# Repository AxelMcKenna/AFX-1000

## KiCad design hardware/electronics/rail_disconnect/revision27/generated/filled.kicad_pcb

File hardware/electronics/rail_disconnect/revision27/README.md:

# E27 disconnect qualification audit and routing candidate

E27 is a separate development candidate, preserving E26, E25 and A11. It retains the 164-part pin/value circuit, all component/pad positions, outline, mounts and bulk-capacitor poses. It adds 925 trace segments and 22 conventional vias over E26: **8,860 segments and 518 vias**. Native checking reports **8 open connections, 21 DRC warnings and zero parity issues**, compared with E26's 21 opens and 30 warnings. The remaining warnings are 20 dangling tracks and one copper sliver. The strict checker fails; this is not a fabrication or full qualification pass.

The repaired main header paths include N12_SRC and N19. Missing OV, reference, allow and MCAP branches remain critical: they can prevent or defeat the power interlock. Do not interpret the smaller open count as a safe power-up release. Every physical, copper-loss, thermal, startup, fabrication and build-ready flag remains false.

## What was actually checked and changed

`native_graph.py` exports connected-component anchors from KiCad's actual connectivity engine and freshly filled board. The bounded repair uses those anchors, rather than assuming the reported nearest airwire endpoints are usable escape points. All additions are ordinary traces/vias; no jumper component or ignored DRC rule closes a net. `reviewed-additions.json` and `replay.py` reconstruct the editable PCB byte-for-byte from frozen E26 plus the exact added copper objects.

Some new traces use In1.Cu, cutting clearances into its AGND pour. In4.Cu remains the other ground plane. This changes return-plane usage and has **not** been qualified for reference impedance, noise or EMI. No component moves or new mechanical clearance claims are made. The proposed P02 strap/stud interfaces are still absent.

A trial that allowed signal routes to cut power pours introduced new power-net opens; that trial was rejected. Short experiment records remain under `generated/experiments/`. The selected board preserves the power-pour reservations, uses the additional inner-layer escapes and retains every actual native finding.

## Actual filled-copper diagnostic

`copper.py` builds a finite-volume resistor network from native **filled polygons**, actual traces and lands, and finite cylindrical plated barrels. It does not replace fills with ideal ribbon rectangles. Assumed process values are 70 µm finished copper, 25 µm plating and 85 °C copper. The PCB has **no specified dielectric stackup**; equal layer spacing is an explicit placeholder for the barrel calculation.

| Positive path, excluding MOSFET channels | 0.20 mm grid | 0.10 mm grid | P02 allocation |
| --- | ---: | ---: | ---: |
| Analog source + common + output | 3.169 mΩ | 3.140 mΩ | ≤3.000 mΩ |
| Digital source + common + output | 1.055 mΩ | 1.017 mΩ | ≤3.000 mΩ |

The analog diagnostic exceeds the allocation at both resolutions. This is a model concern requiring layout/process refinement and a bounded extraction, not an independently certified resistance failure. Rounded lands are rectangularized, cell-center discretization is approximate, annuli/contact regions are idealized, and parallel FET terminal groups are equipotential electrodes. The digital result therefore **does not bound unequal or diagonal switch current sharing**.

The header-return diagnostic uses 0.40/0.20 mm grids. Its finer values are approximately 0.632 mΩ J1→J3 analog return, 0.275 mΩ J2→J4 digital return, and 0.814 mΩ between the protected analog/digital ground headers. These are two-terminal pair resistances under the same approximations, **not multiport transfer impedances or the full P02 strap/contact paths**. No unimplemented stud region is treated as a real electrical terminal. Real four-wire, temperature and current-sharing measurements remain required.

## Manufacturer findings

The [Skyworks Si8751 datasheet](https://www.skyworksinc.com/-/media/SkyWorks/SL/documents/public/data-sheets/Si8751-2.pdf) gives the reviewed timing conditions at a 100 pF gate load. The existing TT=10 kΩ circuit is checked against its static gate-voltage/impedance entries; those values do not bound the actual switch waveform. The [TI CSD18510Q5B table](https://www.ti.com/lit/ds/symlink/csd18510q5b.pdf) gives up to 153 nC at its stated 10 V gate / 20 V drain / 32 A test point. Four digital FETs give a 612 nC comparison, 612 times the 100 pF-at-10 V test charge. That comparison is not an actual application gate-charge measurement or a scaled timing guarantee. The [CSD18540Q5B](https://www.ti.com/lit/ds/symlink/csd18540q5b.pdf) has its own stated test conditions and SOA.

All 14 FET footprints have generic **0.70 × 0.70 mm** source/gate lands. TI's CSD18510Q5B recommended pattern, section 7.2, specifies **1.100 × 0.710 mm** for those lands. The footprints are not that recommended pattern, and no alternate assembly/manufacturer approval is recorded. Pin roles match the reviewed top-view diagram, but terminal tolerances, complete compound drain shape, mask and stencil still need a coordinated land-pattern review and correction/approval. The larger TI compound drain drawing must not be compared as if it were merely the generic footprint's central exposed-pad rectangle.

The native C24 bulk is 4,700 µF ±20%. At the maximum local capacitance and 5.1 V, stored energy is 73.35 mJ; a hypothetical 1 ms linear ramp needs 28.764 A average before load or downstream capacitors. This is not a predicted waveform. The interlock has no independent current limiter, and upstream soft start does not constrain a later FET closure. Avalanche energy is not the linear SOA needed to approve that event. Measure actual VDS, ID and VGS simultaneously and assess the hot transient operating locus.

This board provides a level-controlled **overvoltage-only** interlock. It adds no undervoltage qualification or separate fault latch. Opening the switches does not establish rapid bulk discharge or isolation of every signal-pin backfeed path.

## Reproduce

```sh
uv run --locked python -m hardware.electronics.rail_disconnect.revision27.replay --check
uv run --locked python -m hardware.electronics.rail_disconnect.revision27.check --kicad-cli /path/to/kicad-cli
# Strict native check above intentionally fails while the reported findings remain.
uv run --locked python -m hardware.electronics.rail_disconnect.revision27.device_review
uv run --locked python -m hardware.electronics.rail_disconnect.revision27.copper --steps .2,.1
uv run --locked python -m hardware.electronics.rail_disconnect.revision27.copper --returns
uv run --locked python -m unittest discover -s tests/tooling -p test_disconnect_revision27.py -v
uv run --locked python -m hardware.electronics.rail_disconnect.revision27.qualify
```

`native_graph.py` requires KiCad's supplied Python/pcbnew; the copper diagnostic requires NumPy. Tests independently check exact series/parallel networks, finite barrel resistance, missing-via disconnection, gate/energy scaling, byte-exact replay, parent-item preservation and rejection of suppressed native findings. Synthetic solver fixtures are not physical captures.

`generated/qualification.json` binds the source, native findings and diagnostic outputs without converting them into measured results. Manufacturer/fabricator approval, complete routing, a specified stackup, actual copper/contact bounds, late-closure SOA, thresholds/timing, partial-power behavior, thermal/EMI and complete-system physical measurements are still required.

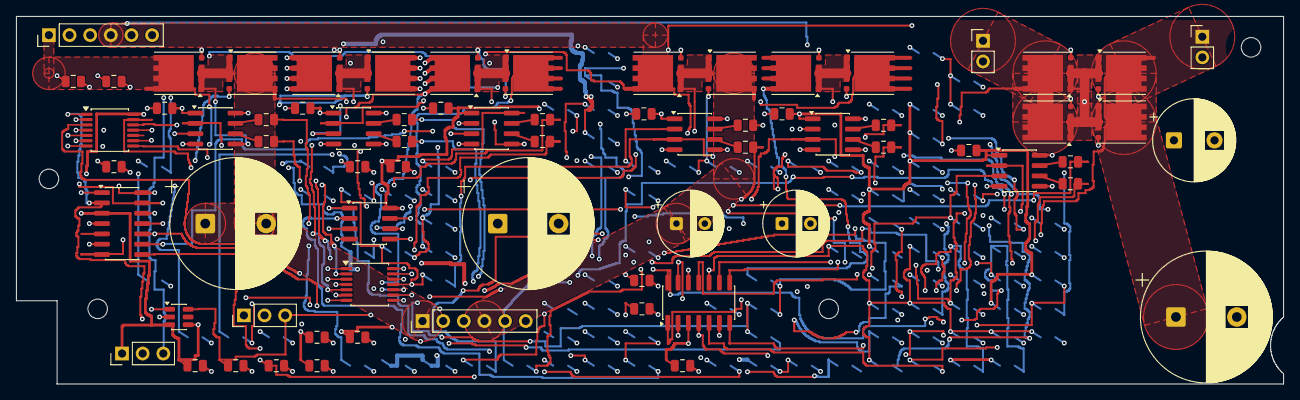
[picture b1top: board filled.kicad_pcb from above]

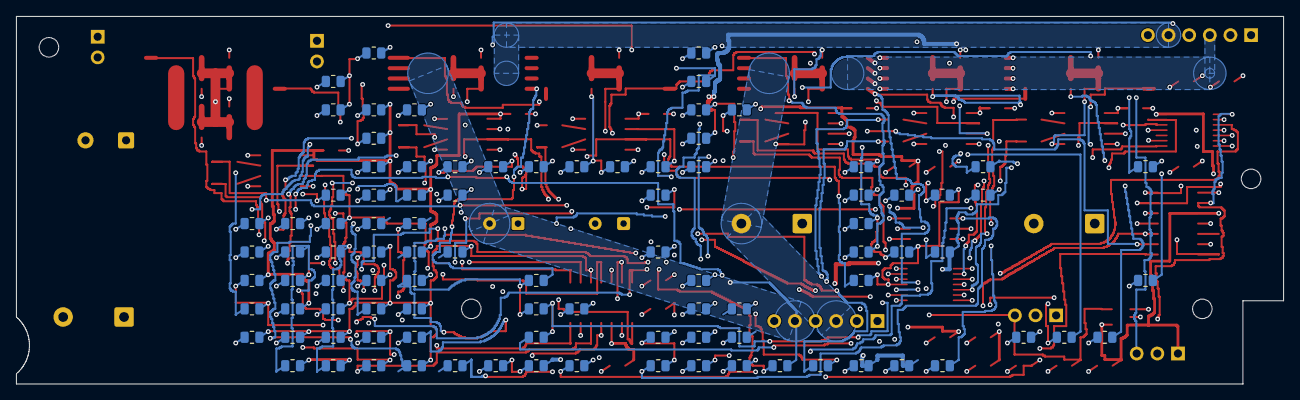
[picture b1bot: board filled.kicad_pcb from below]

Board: 6 copper layers, 156.0 x 45.2 mm, 168 parts (94 on the bottom side), 108 nets.

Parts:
C1, C5, C9, C13, C17, C21, C25, C29, C34, C35, C36, C37: 100nF 16V X7R; C_0805_2012Metric
C2, C3, C6, C7, C10, C11, C14, C15, C18, C19, C22, C23: 10pF 100V C0G 5%; C_0805_2012Metric
C4, C8: 1500uF 35V electrolytic 20% EEUFR1V152S; CP_Radial_D16.0mm_P7.50mm
C12, C16: 220uF 35V electrolytic 20% EEUFR1V221; CP_Radial_D8.0mm_P3.50mm
C20: 1500uF 16V electrolytic 20% EEUFR1C152; CP_Radial_D10.0mm_P5.00mm
C24: 4700uF 16V electrolytic 20% EEUFR1C472; CP_Radial_D16.0mm_P7.50mm
C26: 1uF 16V X7R; C_0805_2012Metric
C27, C28, C30, C31, C32, C33: 100pF 50V C0G 5%; C_0805_2012Metric
C38: 10uF 16V X7R; C_0805_2012Metric
H1, H2, H3, H4: M2_CLEARANCE; M2_Clearance
J1, J3: Header6; PinHeader_1x06_P2.54mm_Vertical
J2, J4: Header2; PinHeader_1x02_P2.54mm_Vertical
J5, J6: Header3; PinHeader_1x03_P2.54mm_Vertical
Q1, Q2, Q3, Q4, Q5, Q6, Q7, Q8: CSD18540Q5B; VSONP-8-1EP_5x6_P1.27mm
Q9, Q10, Q11, Q12, Q13, Q14: CSD18510Q5B; VSONP-8-1EP_5x6_P1.27mm
R1, R9, R17, R25, R33, R41: 22 1%; R_0805_2012Metric
R2, R10, R18, R26, R34, R42, R60, R63, R68, R71, R76, R81, R86, R91: 20M 1%; R_0805_2012Metric
R3, R5, R11, R13, R19, R21, R27, R29, R35, R37, R43, R45, R61, R64, R69, R72, R77, R82, R87, R92: 10k 1%; R_0805_2012Metric
R4, R12, R20, R28, R36, R44: 100 1%; R_0805_2012Metric
R6, R7, R14, R15, R22, R23, R30, R31, R38, R39, R46, R47: 15k 1%; R_0805_2012Metric
R8, R16, R24, R32, R40, R48: 47k 1%; R_0805_2012Metric
R49: 150k 0.01% 5ppm; R_0805_2012Metric
R50: 6.2k 0.01% 5ppm; R_0805_2012Metric
R51, R54, R58, R59, R62, R66, R67, R70, R74, R75, R79, R80, R84, R85, R89, R90, R94: 10k 0.01% 5ppm; R_0805_2012Metric
R52, R55: 1k 1%; R_0805_2012Metric
R53: 100k 0.01% 5ppm; R_0805_2012Metric
R56: 143k 0.01% 5ppm; R_0805_2012Metric
R57: 3.3k 0.01% 5ppm; R_0805_2012Metric
R65: 90.9k 0.01% 5ppm; R_0805_2012Metric
R73, R78: 31.6k 0.01% 5ppm; R_0805_2012Metric
R83: 12.4k 0.01% 5ppm; R_0805_2012Metric
R88: 7.5k 0.01% 5ppm; R_0805_2012Metric
R93: 100k 1%; R_0805_2012Metric
U1, U2, U3, U4, U5, U6: SI8751AB-ISR; SOIC-8_3.9x4.9mm_P1.27mm
U7: REF35125QDBVR; SOT-23-6
U8: OPA2333AID; SOIC-8_3.9x4.9mm_P1.27mm
U9, U10: TLV1824IDR; SOIC-14_3.9x8.7mm_P1.27mm
U11, U12: SN74LVC08APWR; TSSOP-14_4.4x5mm_P0.65mm

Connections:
/5V_DIG: C24.1, J4.1, Q12.3, Q14.3, R47.1, R48.1
/5V_DIG_ALLOW: R44.2, R45.1, U6.3
/5V_DIG_COMMON: Q11.1, Q12.1, Q13.1, Q14.1, R42.2, U6.5
/5V_DIG_DRIVE: R41.1, U6.8
/5V_DIG_GATE: Q11.2, Q12.2, Q13.2, Q14.2, R41.2, R42.1
/5V_DIG_MCAP1: C22.2, U6.7
/5V_DIG_MCAP1_LIMIT: C22.1, R46.2
/5V_DIG_MCAP2: C23.2, U6.6
/5V_DIG_MCAP2_LIMIT: C23.1, R47.2
/5V_DIG_OV_OK: R81.1, R82.2, U10.1, U11.10
/5V_DIG_OV_REF: R80.2, R81.2, U10.7
/5V_DIG_OV_SENSE: C33.1, R78.2, R79.1, U10.6
/5V_DIG_SRC: J2.1, Q11.3, Q13.3, R46.1, R78.1
/5V_DIG_TT: R43.1, U6.2
/AGND: C1.2, C4.2, C5.2, C8.1, C9.2, C12.2, C13.2, C16.1, C17.2, C20.2, C21.2, C24.2, C25.2, C26.2, C27.2, C28.2, C29.2, C30.2, C31.2, C32.2, C33.2, C34.2, C35.2, C36.2, C37.2, C38.2, J1.2, J2.2, J3.2, J4.2, J5.2, J6.1, R3.2, R5.2, R8.2, R11.2, R13.2, R16.2, R19.2, R21.2, R24.2, R27.2, R29.2, R32.2, R35.2, R37.2, R40.2, R43.2, R45.2, R48.2, R58.2, R66.2, R74.2, R79.2, R84.2, R89.2, R93.2, R94.2, U1.4, U2.4, U3.4, U4.4, U5.4, U6.4, U7.1, U7.2, U8.3, U8.4, U8.5, U9.12, U10.12, U11.7, U12.7
/ALL_RAILS_ALLOW: J6.2, R4.1, R12.1, R20.1, R28.1, R36.1, R44.1, U12.11
/N12: C16.2, J3.5, Q8.3, R31.1, R32.1
/N12_ALLOW: R28.2, R29.1, U4.3
/N12_COMMON: Q7.1, Q8.1, R26.2, U4.5
/N12_DRIVE: R25.1, U4.8
/N12_GATE: Q7.2, Q8.2, R25.2, R26.1
/N12_INV: R54.1, R55.1, U8.7
/N12_MCAP1: C14.2, U4.7
/N12_MCAP1_LIMIT: C14.1, R30.2
/N12_MCAP2: C15.2, U4.6
/N12_MCAP2_LIMIT: C15.1, R31.2
/N12_OV_OK: R71.1, R72.2, U9.13, U11.5
/N12_OV_REF: R70.2, R71.2, U9.11
/N12_OV_SENSE: C28.1, R55.2, U9.10
/N12_SRC: J1.5, Q7.3, R30.1, R53.1
/N12_SUM: R53.2, R54.2, U8.6
/N12_TT: R27.1, U4.2
/N19: C8.2, J3.3, Q4.3, R15.1, R16.1
/N19_ALLOW: R12.2, R13.1, U2.3
/N19_COMMON: Q3.1, Q4.1, R10.2, U2.5
/N19_DRIVE: R9.1, U2.8
/N19_GATE: Q3.2, Q4.2, R9.2, R10.1
/N19_INPUT_MID: R49.2, R50.1
/N19_INV: R51.1, R52.1, U8.1
/N19_MCAP1: C6.2, U2.7
/N19_MCAP1_LIMIT: C6.1, R14.2
/N19_MCAP2: C7.2, U2.6
/N19_MCAP2_LIMIT: C7.1, R15.2
/N19_OV_OK: R63.1, R64.2, U9.1, U11.2
/N19_OV_REF: R62.2, R63.2, U9.7
/N19_OV_SENSE: C27.1, R52.2, U9.6
/N19_SRC: J1.3, Q3.3, R14.1, R49.1
/N19_SUM: R50.2, R51.2, U8.2
/N19_TT: R11.1, U2.2
/OK_5: U11.8, U12.4
/OK_12: U11.6, U12.2
/OK_19: U11.3, U12.1
/OK_ALL_OV: U12.8, U12.12
/OK_ANALOG: U12.3, U12.9
/OK_AUXILIARY: U12.6, U12.10
/OK_REF: U11.11, U12.5
/P12: C12.1, J3.4, Q6.3, R23.1, R24.1
/P12_ALLOW: R20.2, R21.1, U3.3
/P12_COMMON: Q5.1, Q6.1, R18.2, U3.5
/P12_DRIVE: R17.1, U3.8
/P12_GATE: Q5.2, Q6.2, R17.2, R18.1
/P12_MCAP1: C10.2, U3.7
/P12_MCAP1_LIMIT: C10.1, R22.2
/P12_MCAP2: C11.2, U3.6
/P12_MCAP2_LIMIT: C11.1, R23.2
/P12_OV_OK: R68.1, R69.2, U9.14, U11.4
/P12_OV_REF: R67.2, R68.2, U9.9
/P12_OV_SENSE: C31.1, R65.2, R66.1, U9.8
/P12_SRC: J1.4, Q5.3, R22.1, R65.1
/P12_TT: R19.1, U3.2
/P19: C4.1, J3.1, Q2.3, R7.1, R8.1
/P19_ALLOW: R4.2, R5.1, U1.3
/P19_COMMON: Q1.1, Q2.1, R2.2, U1.5
/P19_DRIVE: R1.1, U1.8
/P19_GATE: Q1.2, Q2.2, R1.2, R2.1
/P19_MCAP1: C2.2, U1.7
/P19_MCAP1_LIMIT: C2.1, R6.2
/P19_MCAP2: C3.2, U1.6
/P19_MCAP2_LIMIT: C3.1, R7.2
/P19_OV_OK: R60.1, R61.2, U9.2, U11.1
/P19_OV_REF: R59.2, R60.2, U9.5
/P19_OV_SENSE: C30.1, R57.2, R58.1, U9.4
/P19_SENSE_MID: R56.2, R57.1
/P19_SRC: J1.1, Q1.3, R6.1, R56.1
/P19_TT: R3.1, U1.2
/POWER_RUN: J5.3, R93.1, U12.13
/PROTECT_REF: C26.1, J6.3, R59.1, R62.1, R67.1, R70.1, R75.1, R80.1, R85.1, R94.1, U7.6, U10.10
/REF_HIGH_AUX: R88.2, R89.1, R90.1
/REF_HIGH_OK: R91.1, R92.2, U10.13, U11.13
/REF_HIGH_POSITIVE: R90.2, R91.2, U10.11
/REF_LOW_AUX: R83.2, R84.1, U10.8
/REF_LOW_OK: R86.1, R87.2, U10.14, U11.12
/REF_LOW_POSITIVE: R85.2, R86.2, U10.9
/V2V5_AUX: C1.1, C5.1, C9.1, C13.1, C17.1, C21.1, C25.1, C29.1, C34.1, C35.1, C36.1, C37.1, C38.1, J5.1, R61.1, R64.1, R69.1, R72.1, R77.1, R82.1, R83.1, R87.1, R88.1, R92.1, U1.1, U2.1, U3.1, U4.1, U5.1, U6.1, U7.3, U7.4, U8.8, U9.3, U10.3, U11.14, U12.14
/V5_REG: C20.1, J3.6, Q10.3, R39.1, R40.1
/V5_REG_ALLOW: R36.2, R37.1, U5.3
/V5_REG_COMMON: Q9.1, Q10.1, R34.2, U5.5
/V5_REG_DRIVE: R33.1, U5.8
/V5_REG_GATE: Q9.2, Q10.2, R33.2, R34.1
/V5_REG_MCAP1: C18.2, U5.7
/V5_REG_MCAP1_LIMIT: C18.1, R38.2
/V5_REG_MCAP2: C19.2, U5.6
/V5_REG_MCAP2_LIMIT: C19.1, R39.2
/V5_REG_OV_OK: R76.1, R77.2, U10.2, U11.9
/V5_REG_OV_REF: R75.2, R76.2, U10.5
/V5_REG_OV_SENSE: C32.1, R73.2, R74.1, U10.4
/V5_REG_SRC: J1.6, Q9.3, R38.1, R73.1
/V5_REG_TT: R35.1, U5.2
